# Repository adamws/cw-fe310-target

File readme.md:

## fe310 risc-v victim for chipwhisperer's ufo board

### Known issues for revision 0.1:
1. JTAG_VREF and VREF for ufo connector not connected to +3V3

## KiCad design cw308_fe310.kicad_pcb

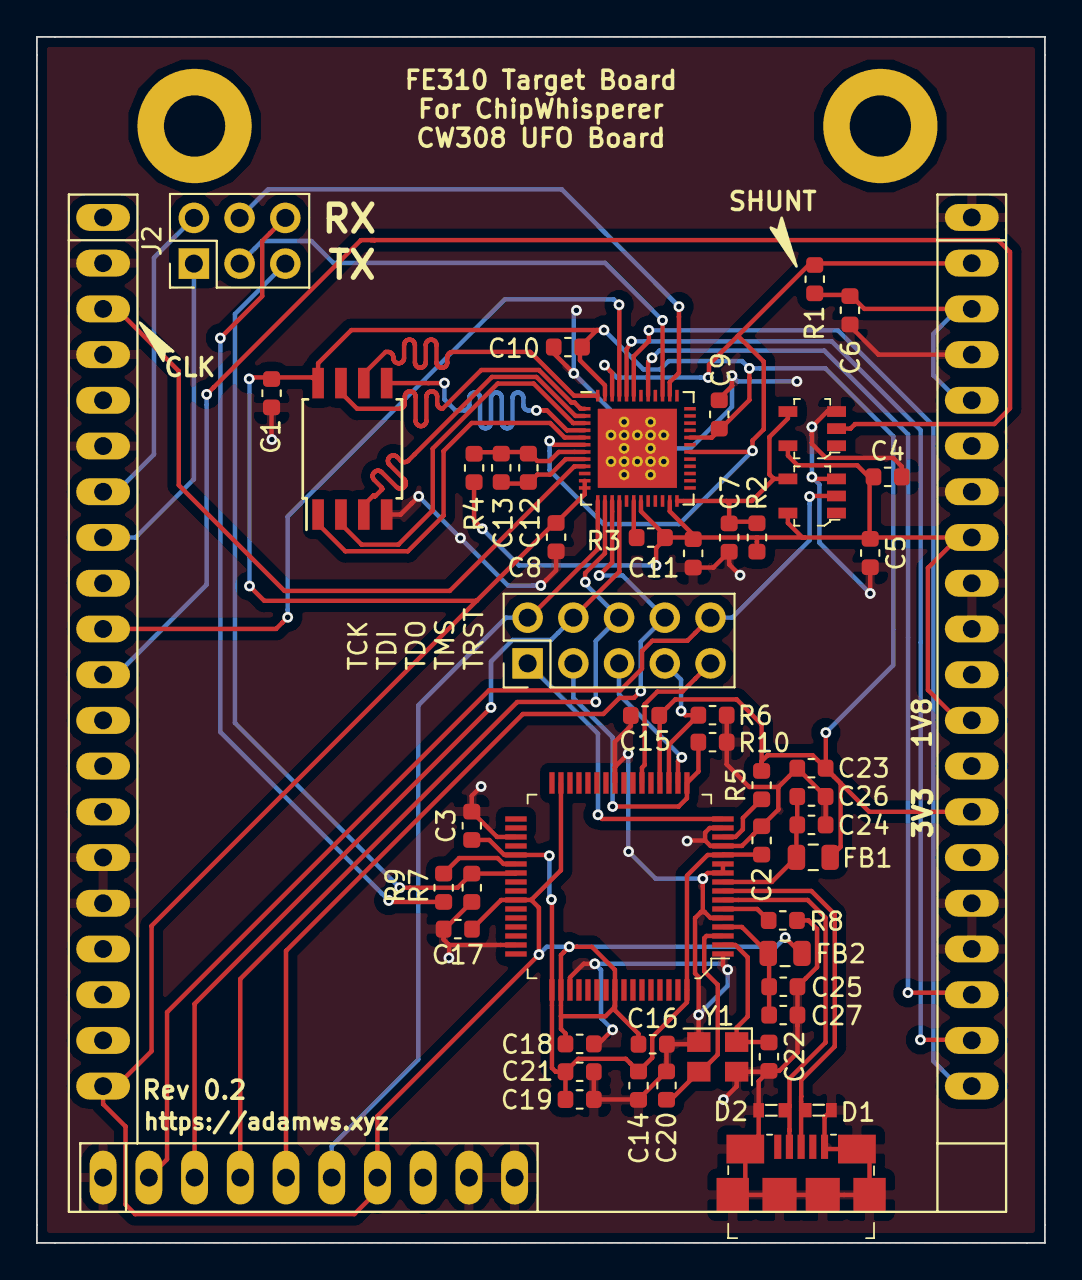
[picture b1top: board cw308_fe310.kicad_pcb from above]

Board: 2 copper layers, 56.0 x 67.0 mm, 51 parts (0 on the bottom side), 47 nets.

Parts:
C1, C2, C3, C4, C5, C8, C9, C10, C11, C12, C13, C14, C15, C16, C17, C18, C19, C23, C24, C25: 0.1uF; C_0603_1608Metric
C6: 100n; C_0603_1608Metric
C7: 10nF; C_0603_1608Metric
C20, C22: 27pF; C_0603_1608Metric
C21, C26, C27: 4.7uF; C_0603_1608Metric
D1, D2: PGB1010603MR; 0603
FB1, FB2: Ferrite_Bead; L_0805_2012Metric
J1: CW308T_CONNBOARD
J2: Conn_02x03_Odd_Even; PinHeader_2x03_P2.54mm_Vertical
J4: Conn_02x05_Odd_Even; PinHeader_2x05_P2.54mm_Vertical
J5: 10118192-0001LF; USB_Micro_B_Female_10118192
R1: 51R; R_0603_1608Metric
R2: 100K; R_0603_1608Metric
R3: 100k; R_0603_1608Metric
R4: 100; R_0603_1608Metric
R5, R6, R7, R9, R10: 1K; R_0603_1608Metric
R8: 12K; R_0603_1608Metric
U1: IS25LP128; SOIJ-8_5.3x5.3mm_P1.27mm
U2, U3: SN74LVC1G07DBVR; SOT-753
U4: FE310-G000; QFN-48-1EP_6x6mm_P0.4mm_EP4.66x4.66mm_ThermalVias
U5: FT2232HL-REEL; LQFP-64_10x10mm
Y1: 12MHz; Oscillator_SMD_Abracon_ASE-4Pin_3.2x2.5mm

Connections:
+1V8: C4.1, C5.1, C11.2, J1.C8, J1.C12, R2.1, R3.2, R4.1, U2.5, U3.5, U4.19, U4.23
+3V3: C1.1, C8.1, C9.1, C10.1, C15.1, C16.1, C17.1, C18.1, C23.1, FB1.2, FB2.2, J1.A20, J1.B7, J1.C14, R5.2, U1.8, U4.11, U4.12, U4.32, U4.47, U5.20, U5.31, U5.42, U5.50, U5.56
CLKIN: J1.A3, U4.9
DM: D2.1, J5.2, U5.7
DP: D1.1, J5.3, U5.8
FLASH_IO0: U1.5, U4.4
FLASH_IO1: U1.2, U4.3
FLASH_IO2: U1.3, U4.2
FLASH_IO3: U1.7, U4.1
FLASH_S: U1.1, U4.5
FLASH_SCK: U1.6, U4.48
FT_JTAG_TCK: J4.1, U5.16
FT_JTAG_TDI: J4.3, R10.1, U5.17
FT_JTAG_TDO: J4.5, U5.18
FT_JTAG_TMS: J4.7, R6.1, U5.19
FT_RST: J4.9, U5.22
FT_RX: J2.5, R7.1, U5.39
FT_TX: J2.6, R9.2
GND: C1.2, C2.2, C3.2, C4.2, C5.2, C6.1, C7.2, C8.2, C9.2, C10.2, C11.1, C14.2, C15.2, C16.2, C17.2, C18.2, C19.1, C20.2, C21.1, C22.2, C23.2, C24.2, C25.2, C26.2, C27.2, D1.2, D2.2, J1.A2, J1.A4, J1.A6, J1.A15, J1.A16, J1.B1, J1.B9, J1.B10, J1.C1, J1.C4, J1.C7, J1.C9, J1.C10, J1.C16, J1.C17, J5.5, J5.SH, R6.2, R7.2, R8.2, R10.2, U1.4, U2.3, U3.3, U4.49, U5.1, U5.5, U5.10, U5.11, U5.13, U5.15, U5.25, U5.35, U5.47, U5.51, Y1.2, Y1.4
GPIO1: J1.A7, J2.2
GPIO2: J1.A8, J2.1
GPIO4: J1.A10, U4.45
JTAG_TCK: J1.B6, J4.2, U4.13
JTAG_TDI: J1.B3, J4.4, U4.16
JTAG_TDO: J1.B4, J4.6, U4.14
JTAG_TMS: J1.B5, J4.8, U4.15
JTAG_TRST: J1.B2, J4.10, U3.2
LED1: J1.C18, U4.41
LED2: J1.C19, U4.44
LED3: J1.C20, U4.43
unnamed: C6.2, J1.C3, J1.C5, R1.2
unnamed: C7.1, R2.2, U2.4, U3.4, U4.24
unnamed: C12.1, C13.1, R4.2, U4.7
unnamed: C20.1, U5.3, Y1.3
unnamed: R3.1, U4.18
unnamed: R5.1, U5.14
unnamed: R8.1, U5.6
unnamed: R9.1, U5.38
OSCI: C22.1, U5.2, Y1.1
PLL_AVSS: C12.2, C13.2, U4.8
RX: J2.4, U4.38
TX: J2.3, U4.39
UFO.RST: J1.A11, U2.2
VCC_CLEAN: J1.C2, R1.1, U4.6, U4.30, U4.46
VCORE_FT: C2.1, C3.1, C14.1, C19.2, C21.2, U5.12, U5.37, U5.49, U5.64
VPHY: C25.1, C27.1, FB2.1, U5.4
VPLL: C24.1, C26.1, FB1.1, U5.9

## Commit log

2018-12-01 empty project
2018-12-01 first draft of schematic
2018-12-01 rename project
2018-12-01 added readme.md
2018-12-02 progresx
2018-12-04 progress
2018-12-08 progress update
2018-12-08 simplified prototype ready
2019-02-07 revision 0.1
2019-02-07 locked smd footprints, added gerbers used for revision 0.1
2019-03-17 initial commit for revision 0.2 (ftdi added)
2019-03-17 added project lib table, removed bottom mounting hole from cw connector
2019-03-17 added missing footprints, fixed netlist issue with missing pads for cw connector
2019-03-18 done routing
2019-03-18 minor changes
2019-03-18 order made
2019-03-26 Simplified (#1)
    revision 0.1
2019-04-09 Update readme.md
    (communication problem was software issue)
2019-05-29 fixed values of fdti osc capacitors
2019-05-29 reloaded netlist, re-routed uforst, regenerated fill zones
